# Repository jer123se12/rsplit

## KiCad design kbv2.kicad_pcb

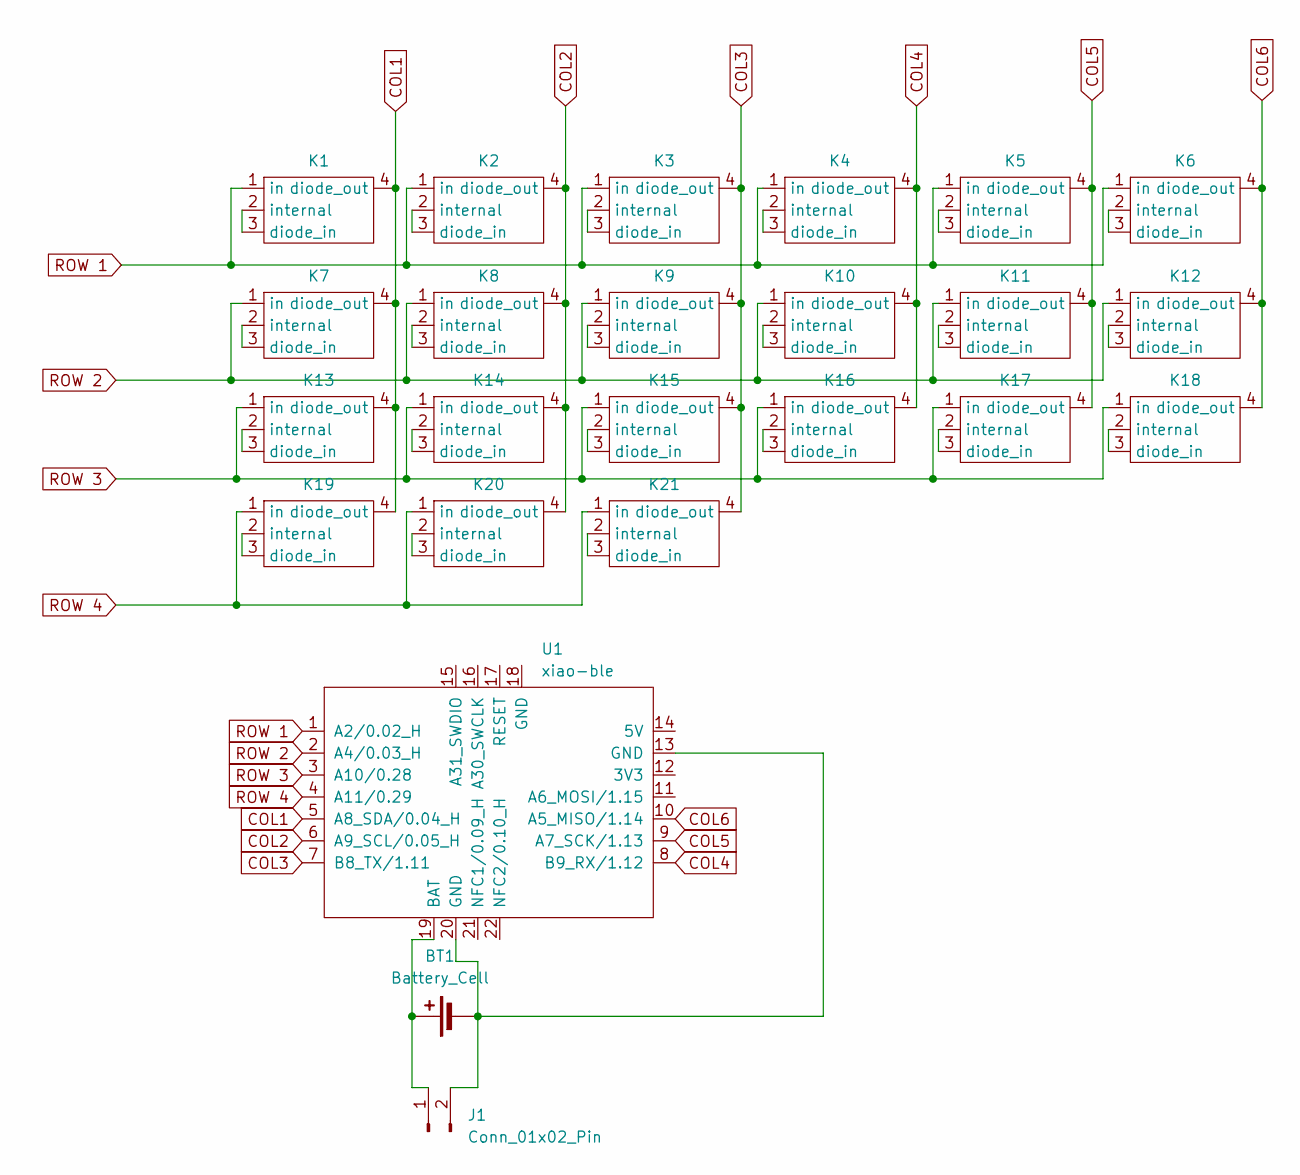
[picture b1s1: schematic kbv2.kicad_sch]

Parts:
BT1: Battery_Cell; mybatteryholder; LCSC C964792
J1: Conn_01x02_Pin; Hirose_DF13-02P-1.25DSA_1x02_P1.25mm_Vertical
K1, K2, K3, K4, K5, K6, K7, K8, K9, K10, K11, K12, K13, K14, K15, K16, K17, K18, K19, K20, K21: SW_Gateron_LowProfile_THT_wdiode_both_sides; LCSC C2919016
U1: xiao-ble; xiao-ble-smd

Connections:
COL1: K1.4 (diode_out), K7.4 (diode_out), K13.4 (diode_out), K19.4 (diode_out), U1.5 (A8_SDA/0.04_H)
COL2: K2.4 (diode_out), K8.4 (diode_out), K14.4 (diode_out), K20.4 (diode_out), U1.6 (A9_SCL/0.05_H)
COL3: K3.4 (diode_out), K9.4 (diode_out), K15.4 (diode_out), K21.4 (diode_out), U1.7 (B8_TX/1.11)
COL4: K4.4 (diode_out), K10.4 (diode_out), K16.4 (diode_out), U1.8 (B9_RX/1.12)
COL5: K5.4 (diode_out), K11.4 (diode_out), K17.4 (diode_out), U1.9 (A7_SCK/1.13)
COL6: K6.4 (diode_out), K12.4 (diode_out), K18.4 (diode_out), U1.10 (A5_MISO/1.14)
unnamed: BT1.1 (+), J1.1, U1.19 (BAT)
unnamed: BT1.2 (-), J1.2, U1.13 (GND), U1.20 (GND)
unnamed: K1.2 (internal), K1.3 (diode_in)
unnamed: K2.2 (internal), K2.3 (diode_in)
unnamed: K3.2 (internal), K3.3 (diode_in)
unnamed: K4.2 (internal), K4.3 (diode_in)
unnamed: K5.2 (internal), K5.3 (diode_in)
unnamed: K6.2 (internal), K6.3 (diode_in)
unnamed: K7.2 (internal), K7.3 (diode_in)
unnamed: K8.2 (internal), K8.3 (diode_in)
unnamed: K9.2 (internal), K9.3 (diode_in)
unnamed: K10.2 (internal), K10.3 (diode_in)
unnamed: K11.2 (internal), K11.3 (diode_in)
unnamed: K12.2 (internal), K12.3 (diode_in)
unnamed: K13.2 (internal), K13.3 (diode_in)
unnamed: K14.2 (internal), K14.3 (diode_in)
unnamed: K15.2 (internal), K15.3 (diode_in)
unnamed: K16.2 (internal), K16.3 (diode_in)
unnamed: K17.2 (internal), K17.3 (diode_in)
unnamed: K18.2 (internal), K18.3 (diode_in)
unnamed: K19.2 (internal), K19.3 (diode_in)
unnamed: K20.2 (internal), K20.3 (diode_in)
unnamed: K21.2 (internal), K21.3 (diode_in)
ROW 1: K1.1 (in), K2.1 (in), K3.1 (in), K4.1 (in), K5.1 (in), K6.1 (in), U1.1 (A2/0.02_H)
ROW 2: K7.1 (in), K8.1 (in), K9.1 (in), K10.1 (in), K11.1 (in), K12.1 (in), U1.2 (A4/0.03_H)
ROW 3: K13.1 (in), K14.1 (in), K15.1 (in), K16.1 (in), K17.1 (in), K18.1 (in), U1.3 (A10/0.28)
ROW 4: K19.1 (in), K20.1 (in), K21.1 (in), U1.4 (A11/0.29)

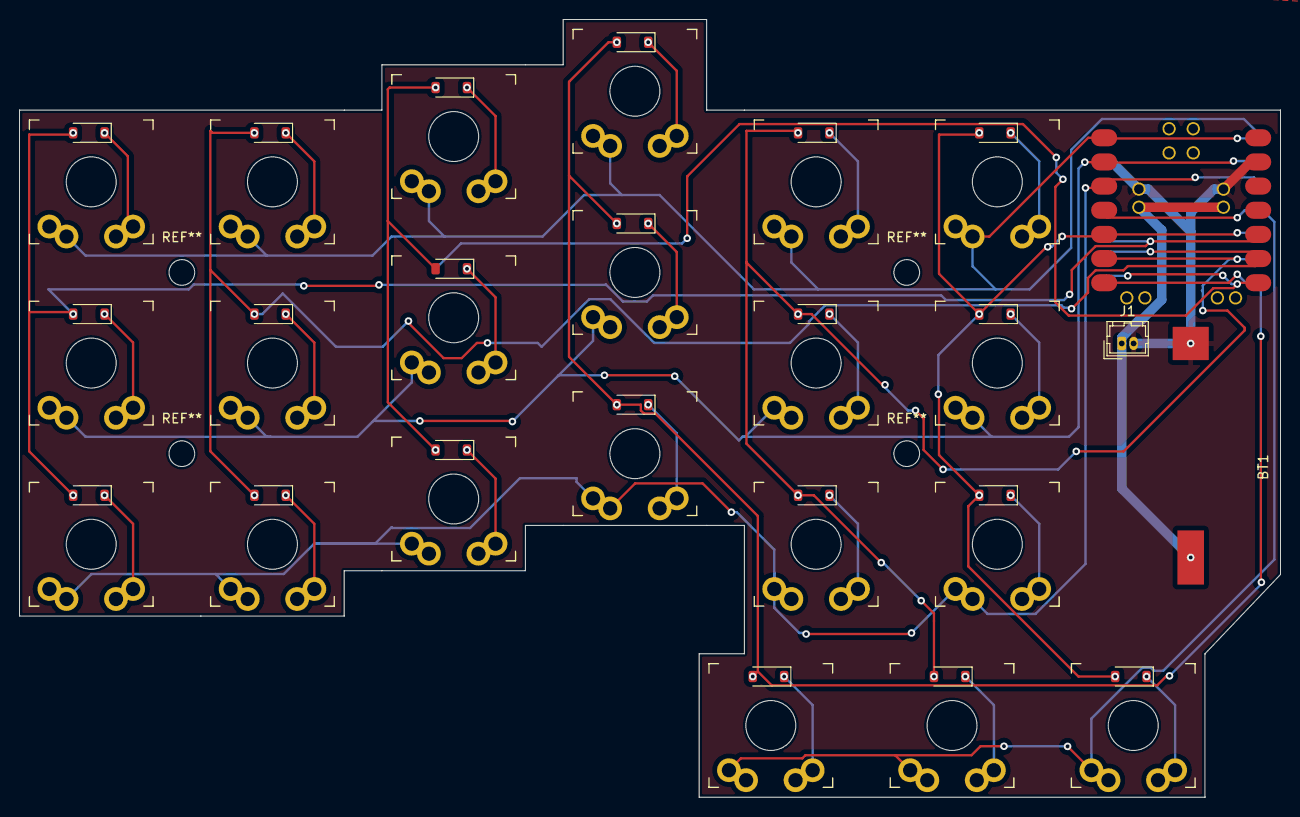
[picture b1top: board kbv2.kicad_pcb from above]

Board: 2 copper layers, 132.6 x 81.8 mm, 24 parts (0 on the bottom side), 33 nets.

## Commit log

2023-09-09 empty
2023-09-15 sent for printing at jlc
